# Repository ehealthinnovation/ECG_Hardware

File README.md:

ECG_Hardware
============

We are building ECG hardware with BTLE

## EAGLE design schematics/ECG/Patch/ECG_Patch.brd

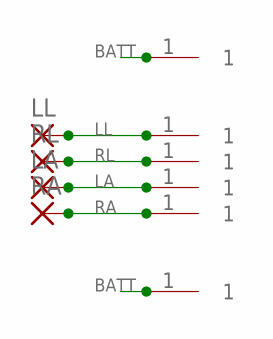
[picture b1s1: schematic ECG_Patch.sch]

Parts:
LA: 1,6/0,8
LL: 1,6/0,8
P1, P2, P3, P4, P5, P6: PISTON_RA_TH
RA: 1,6/0,8
RL: 1,6/0,8

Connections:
BATT: P1.1, P6.1
LA: LA.1, P4.1
LL: LL.1, P3.1
RA: P5.1, RA.1
RL: P2.1, RL.1

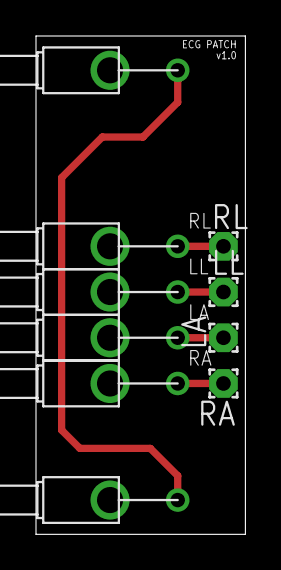
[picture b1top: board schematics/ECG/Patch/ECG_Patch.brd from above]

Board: 2 copper layers, 11.6 x 27.7 mm, 10 parts (0 on the bottom side), 5 nets.

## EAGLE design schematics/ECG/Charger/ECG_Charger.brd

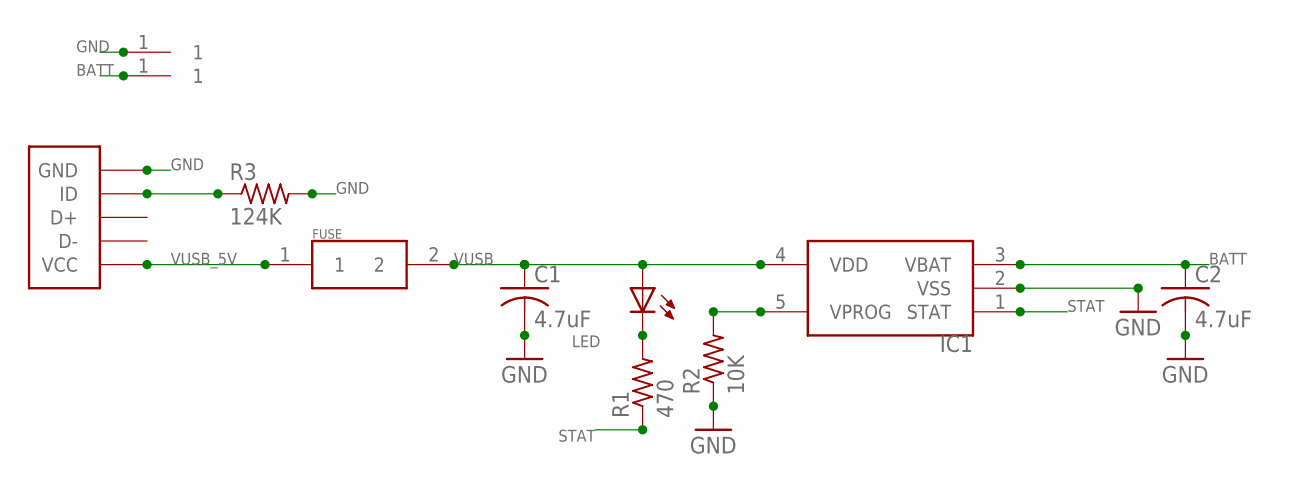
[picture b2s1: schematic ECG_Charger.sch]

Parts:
C1, C2: 4.7uF; C0402
CONN1, CONN2: PISTON_RA_TH
CONN3: USB_MICROC; USB_MICROB_FEMALE_RA_SMT
FUSE: FUSE-MF_SERIES; 1206
IC1: MCP73832_SOT23-5; SOT23-5
LED: LED_SMT_0805; SMT_LED_0805
R1: 470; R0402
R2: 10K; R0402
R3: 124K; R0402

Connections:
BATT: C2.1, CONN2.1, IC1.3 (VBAT)
GND: C1.2, C2.2, CONN1.1, CONN3.P$5 (GND), IC1.2 (VSS), R2.1, R3.2
unnamed: CONN3.P$4 (ID), R3.1
unnamed: LED.C, R1.2
STAT: IC1.1 (STAT), R1.1
VPROG: IC1.5 (VPROG), R2.2
VUSB: C1.1, FUSE.2, IC1.4 (VDD), LED.A
VUSB_5V: CONN3.P$1 (VCC), FUSE.1

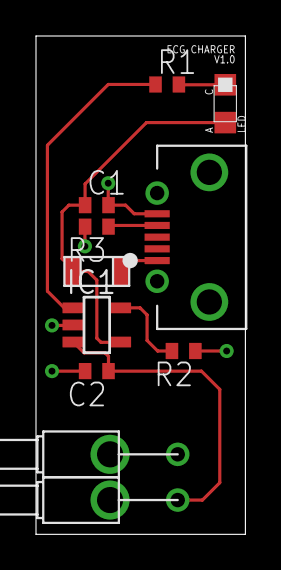
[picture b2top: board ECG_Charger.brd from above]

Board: 2 copper layers, 11.6 x 27.7 mm, 11 parts (0 on the bottom side), 8 nets.

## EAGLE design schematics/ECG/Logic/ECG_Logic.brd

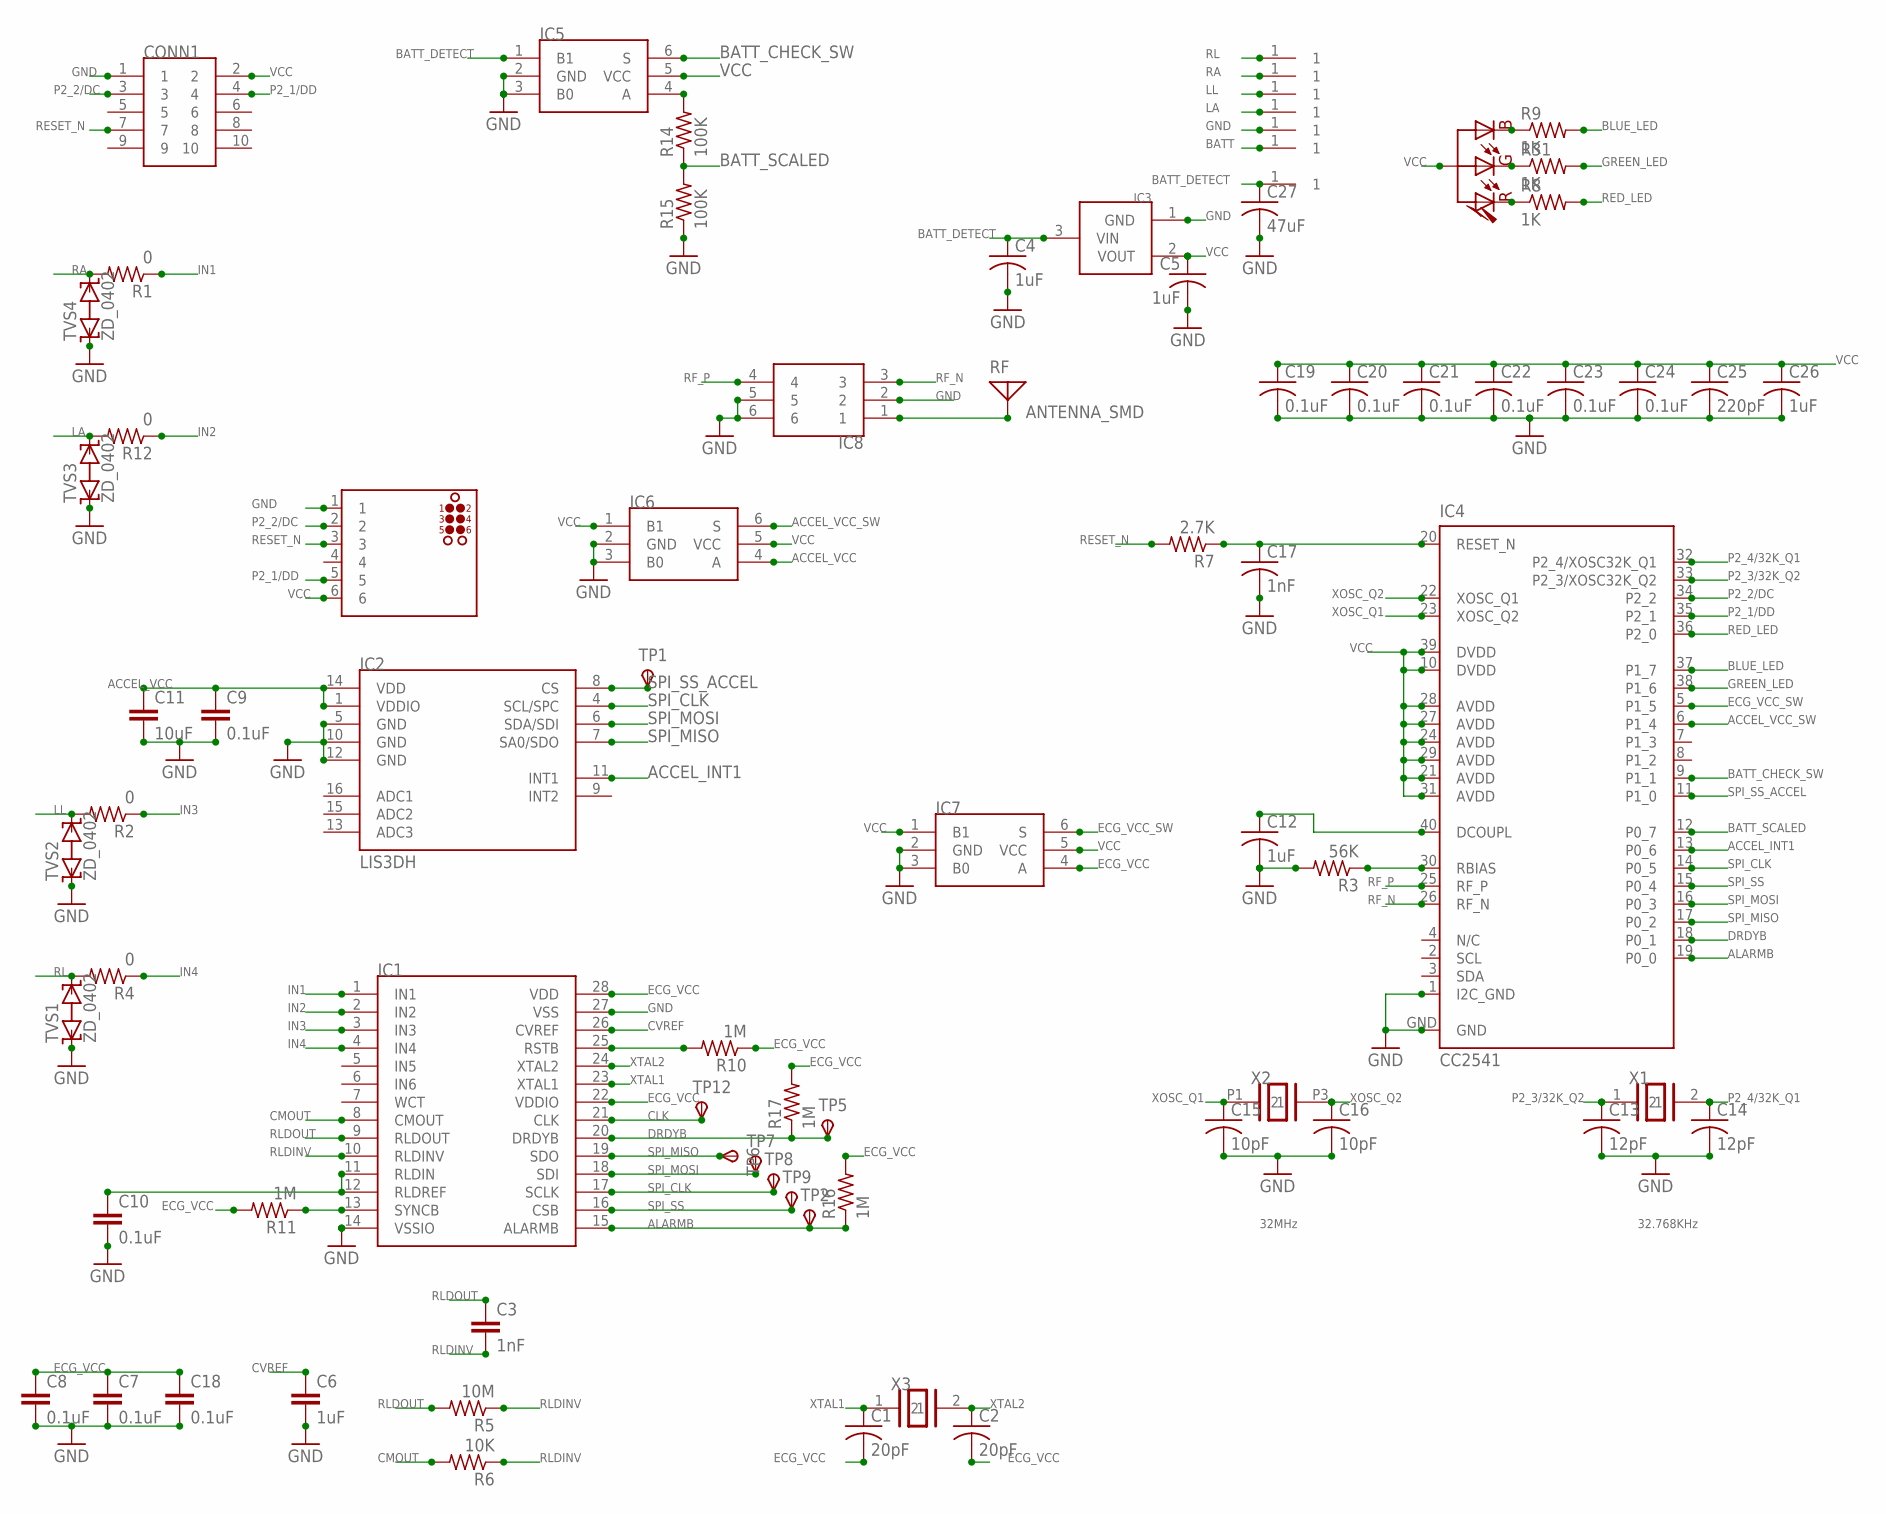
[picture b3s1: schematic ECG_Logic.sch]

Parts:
C1, C2: 20pF; C0201
C3, C17: 1nF; C0201
C4, C5, C6, C12, C26: 1uF; C0201
C7, C8, C9, C10, C18, C19, C20, C21, C22, C23, C24: 0.1uF; C0201
C11: 10uF; C0402
C13, C14: 12pF; C0201
C15, C16: 10pF; C0201
C25: 220pF; C0201
C27: 47uF; C0805
CONN1: 10POS_1.27MM_SMD; 1.27MM_SMD
IC1: ADS1293; WQFN28
IC2: LIS3DH; LGA16-3MM
IC3: MCP1703; SOT23
IC4: CC2541; RHA_S-PVQFN-N40
IC5, IC6, IC7: FSA4157; SC70-6
IC8: BALUN_2450BM_SERIES_SMD; BALUN_SMD_2450BM_SERIES
P1, P2, P3, P4, P5, P6, P7: TARGET_RA
PROG: TC2030-MCP-NL
R1, R2, R4, R12: 0; R0201
R3: 56K; R0201
R5: 10M; R0201
R6: 10K; R0201
R7: 2.7K; R0201
R8, R9, R31: 1K; R0201
R10, R11, R16, R17: 1M; R0201
R14, R15: 100K; R0201
RF: ANTENNA_SMD
TP1, TP5, TP6, TP7, TP8, TP9: TPSTP08SQ; TP08SQ
TP2, TP12: TPSTP06R; TP06R
TRI_LED: SML-LX0404SIUPGUSB
TVS1, TVS2, TVS3, TVS4: ZD_0402; 0402
X1: XTAL-2SMD; 2-SMD
X2: XTAL_403; 4-SMD
X3: ECS-40-20-4VX

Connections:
ACCEL_INT1: IC2.11 (INT1), IC4.13 (P0_6)
ACCEL_VCC: C9.1, C11.1, IC2.1 (VDDIO), IC2.14 (VDD), IC6.4 (A)
ACCEL_VCC_SW: IC4.6 (P1_4), IC6.6 (S)
ALARMB: IC1.15 (ALARMB), IC4.19 (P0_0), R16.1, TP2.TP
BATT: P6.1
BATT_CHECK_SW: IC4.9 (P1_1), IC5.6 (S)
BATT_DETECT: C4.1, C27.1, IC3.3 (VIN), IC5.1 (B1), P7.1
BATT_SCALED: IC4.12 (P0_7), R14.1, R15.2
BLUE_LED: IC4.37 (P1_7), R9.2
CLK: IC1.21 (CLK), TP12.TP
CMOUT: IC1.8 (CMOUT), R6.2
CVREF: C6.1, IC1.26 (CVREF)
DCOUPL: C12.1, IC4.40 (DCOUPL)
DRDYB: IC1.20 (DRDYB), IC4.18 (P0_1), R17.1, TP5.TP
ECG_VCC: C1.2, C2.2, C7.1, C8.1, C18.1, IC1.22 (VDDIO), IC1.28 (VDD), IC7.4 (A), R10.1, R11.2, R16.2, R17.2
ECG_VCC_SW: IC4.5 (P1_5), IC7.6 (S)
GND: C4.2, C5.2, C6.2, C7.2, C8.2, C9.2, C10.2, C11.2, C12.2, C13.2, C14.2, C15.2, C16.2, C17.2, C18.2, C19.2, C20.2, C21.2, C22.2, C23.2, C24.2, C25.2, C26.2, C27.2, CONN1.1, IC1.14 (VSSIO), IC1.27 (VSS), IC2.5 (GND), IC2.10 (GND), IC2.12 (GND), IC3.1 (GND), IC4.1 (I2C_GND), IC4.GND, IC5.2 (GND), IC5.3 (B0), IC6.2 (GND), IC6.3 (B0), IC7.2 (GND), IC7.3 (B0), IC8.2, IC8.5, IC8.6, P5.1, PROG.1, R3.2, R15.1, TVS1.1 (A), TVS2.1 (A), TVS3.1 (A), TVS4.1 (A)
GREEN_LED: IC4.38 (P1_6), R31.2
IN1: IC1.1 (IN1), R1.1
IN2: IC1.2 (IN2), R12.1
IN3: IC1.3 (IN3), R2.1
IN4: IC1.4 (IN4), R4.1
LA: P2.1, R12.2, TVS3.2 (C)
LL: P1.1, R2.2, TVS2.2 (C)
unnamed: R9.1, TRI_LED.3 (B)
unnamed: IC5.4 (A), R14.2
unnamed: IC1.25 (RSTB), R10.2
unnamed: IC8.1, RF.1
unnamed: C17.1, IC4.20 (RESET_N), R7.1
unnamed: R31.1, TRI_LED.4 (G)
unnamed: C10.1, IC1.11 (RLDIN), IC1.12 (RLDREF)
unnamed: IC1.13 (SYNCB), R11.1
unnamed: R8.1, TRI_LED.2 (R)
N/C: IC4.4 (N/C)
P2_1/DD: CONN1.4, IC4.35 (P2_1), PROG.5
P2_2/DC: CONN1.3, IC4.34 (P2_2), PROG.2
P2_3/32K_Q2: C13.1, IC4.33 (P2_3/XOSC32K_Q2), X1.1
P2_4/32K_Q1: C14.1, IC4.32 (P2_4/XOSC32K_Q1), X1.2
RA: P3.1, R1.2, TVS4.2 (C)
RED_LED: IC4.36 (P2_0), R8.2
RESET_N: CONN1.7, PROG.3, R7.2
RF_N: IC4.26 (RF_N), IC8.3
RF_P: IC4.25 (RF_P), IC8.4
RL: P4.1, R4.2, TVS1.2 (C)
RLDINV: C3.2, IC1.10 (RLDINV), R5.1, R6.1
RLDOUT: C3.1, IC1.9 (RLDOUT), R5.2
R_BIAS: IC4.30 (RBIAS), R3.1
SPI_CLK: IC1.17 (SCLK), IC2.4 (SCL/SPC), IC4.14 (P0_5), TP8.TP
SPI_MISO: IC1.19 (SDO), IC2.7 (SA0/SDO), IC4.17 (P0_2), TP6.TP
SPI_MOSI: IC1.18 (SDI), IC2.6 (SDA/SDI), IC4.16 (P0_3), TP7.TP
SPI_SS: IC1.16 (CSB), IC4.15 (P0_4), TP9.TP
SPI_SS_ACCEL: IC2.8 (CS), IC4.11 (P1_0), TP1.TP
VCC: C5.1, C19.1, C20.1, C21.1, C22.1, C23.1, C24.1, C25.1, C26.1, CONN1.2, IC3.2 (VOUT), IC4.10 (DVDD), IC4.21 (AVDD), IC4.24 (AVDD), IC4.27 (AVDD), IC4.28 (AVDD), IC4.29 (AVDD), IC4.31 (AVDD), IC4.39 (DVDD), IC5.5 (VCC), IC6.1 (B1), IC6.5 (VCC), IC7.1 (B1), IC7.5 (VCC), PROG.6, TRI_LED.1 (A)
XOSC_Q1: C15.1, IC4.23 (XOSC_Q2), X2.P1 (1)
XOSC_Q2: C16.1, IC4.22 (XOSC_Q1), X2.P3 (2)
XTAL1: C1.1, IC1.23 (XTAL1), X3.1
XTAL2: C2.1, IC1.24 (XTAL2), X3.2

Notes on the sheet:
32MHz
32.768KHz

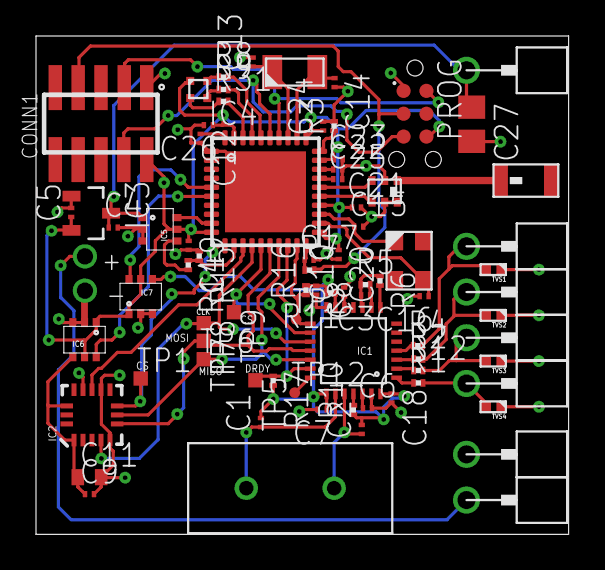
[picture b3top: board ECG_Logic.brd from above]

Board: 2 copper layers, 29.6 x 27.7 mm, 78 parts (0 on the bottom side), 55 nets.

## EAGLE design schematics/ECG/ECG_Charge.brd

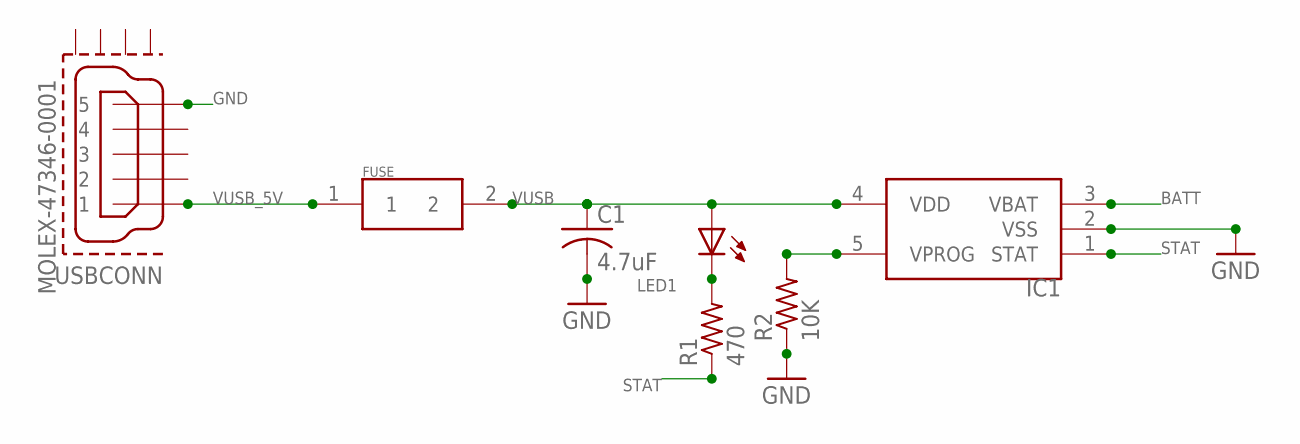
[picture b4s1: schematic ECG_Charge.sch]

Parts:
C1: 4.7uF; C0402
FUSE: FUSE-MF_SERIES; 1206
IC1: MCP73832_SOT23-5; SOT23-5
LED1: LED_SMT_0805; SMT_LED_0805
R1: 470; R0201
R2: 10K; R0201
USBCONN: MOLEX-47346-0001; MOLEX-47364-0001

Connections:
BATT: IC1.3 (VBAT)
GND: C1.2, IC1.2 (VSS), USBCONN.5
unnamed: LED1.C, R1.2
STAT: IC1.1 (STAT), R1.1
VPROG: IC1.5 (VPROG), R2.2
VSS: R2.1
VUSB: C1.1, FUSE.2, IC1.4 (VDD), LED1.A
VUSB_5V: FUSE.1, USBCONN.1

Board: 2 copper layers, 7 parts (7 on the bottom side), 6 nets, no tracks yet.

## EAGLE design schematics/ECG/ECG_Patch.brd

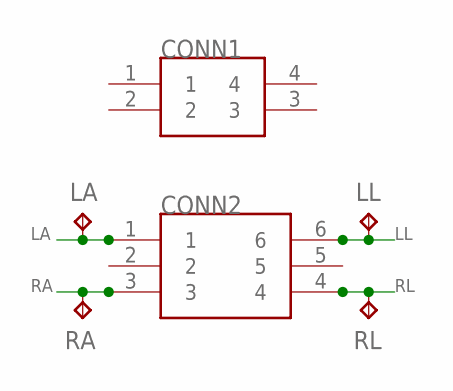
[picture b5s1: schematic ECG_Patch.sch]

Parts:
CONN1: M80-4V; M80-4-V
CONN2: M80-6V; M80-6-V
LA: TPTP20R; TP20R
LL: TPTP20R; TP20R
RA: TPTP20R; TP20R
RL: TPTP20R; TP20R

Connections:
LA: CONN2.1, LA.TP
LL: CONN2.6, LL.TP
RA: CONN2.3, RA.TP
RL: CONN2.4, RL.TP

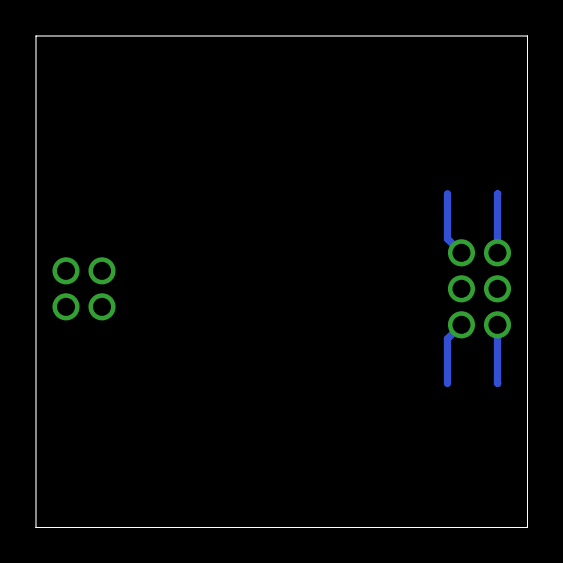
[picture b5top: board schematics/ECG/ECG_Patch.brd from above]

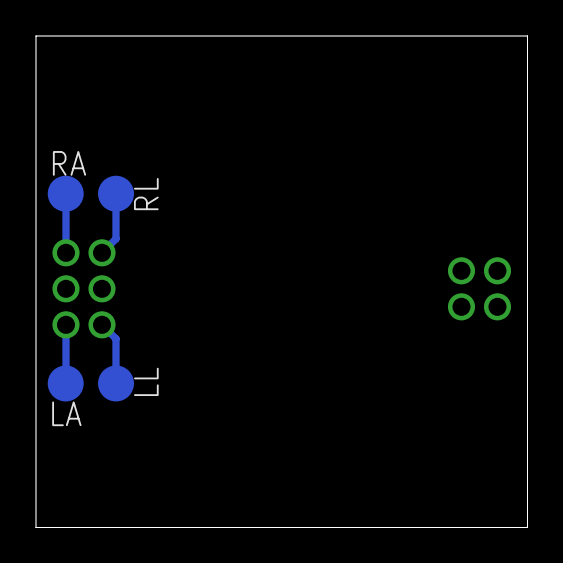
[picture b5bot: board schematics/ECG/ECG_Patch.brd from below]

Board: 4 copper layers, 27.3 x 27.3 mm, 6 parts (4 on the bottom side), 4 nets.

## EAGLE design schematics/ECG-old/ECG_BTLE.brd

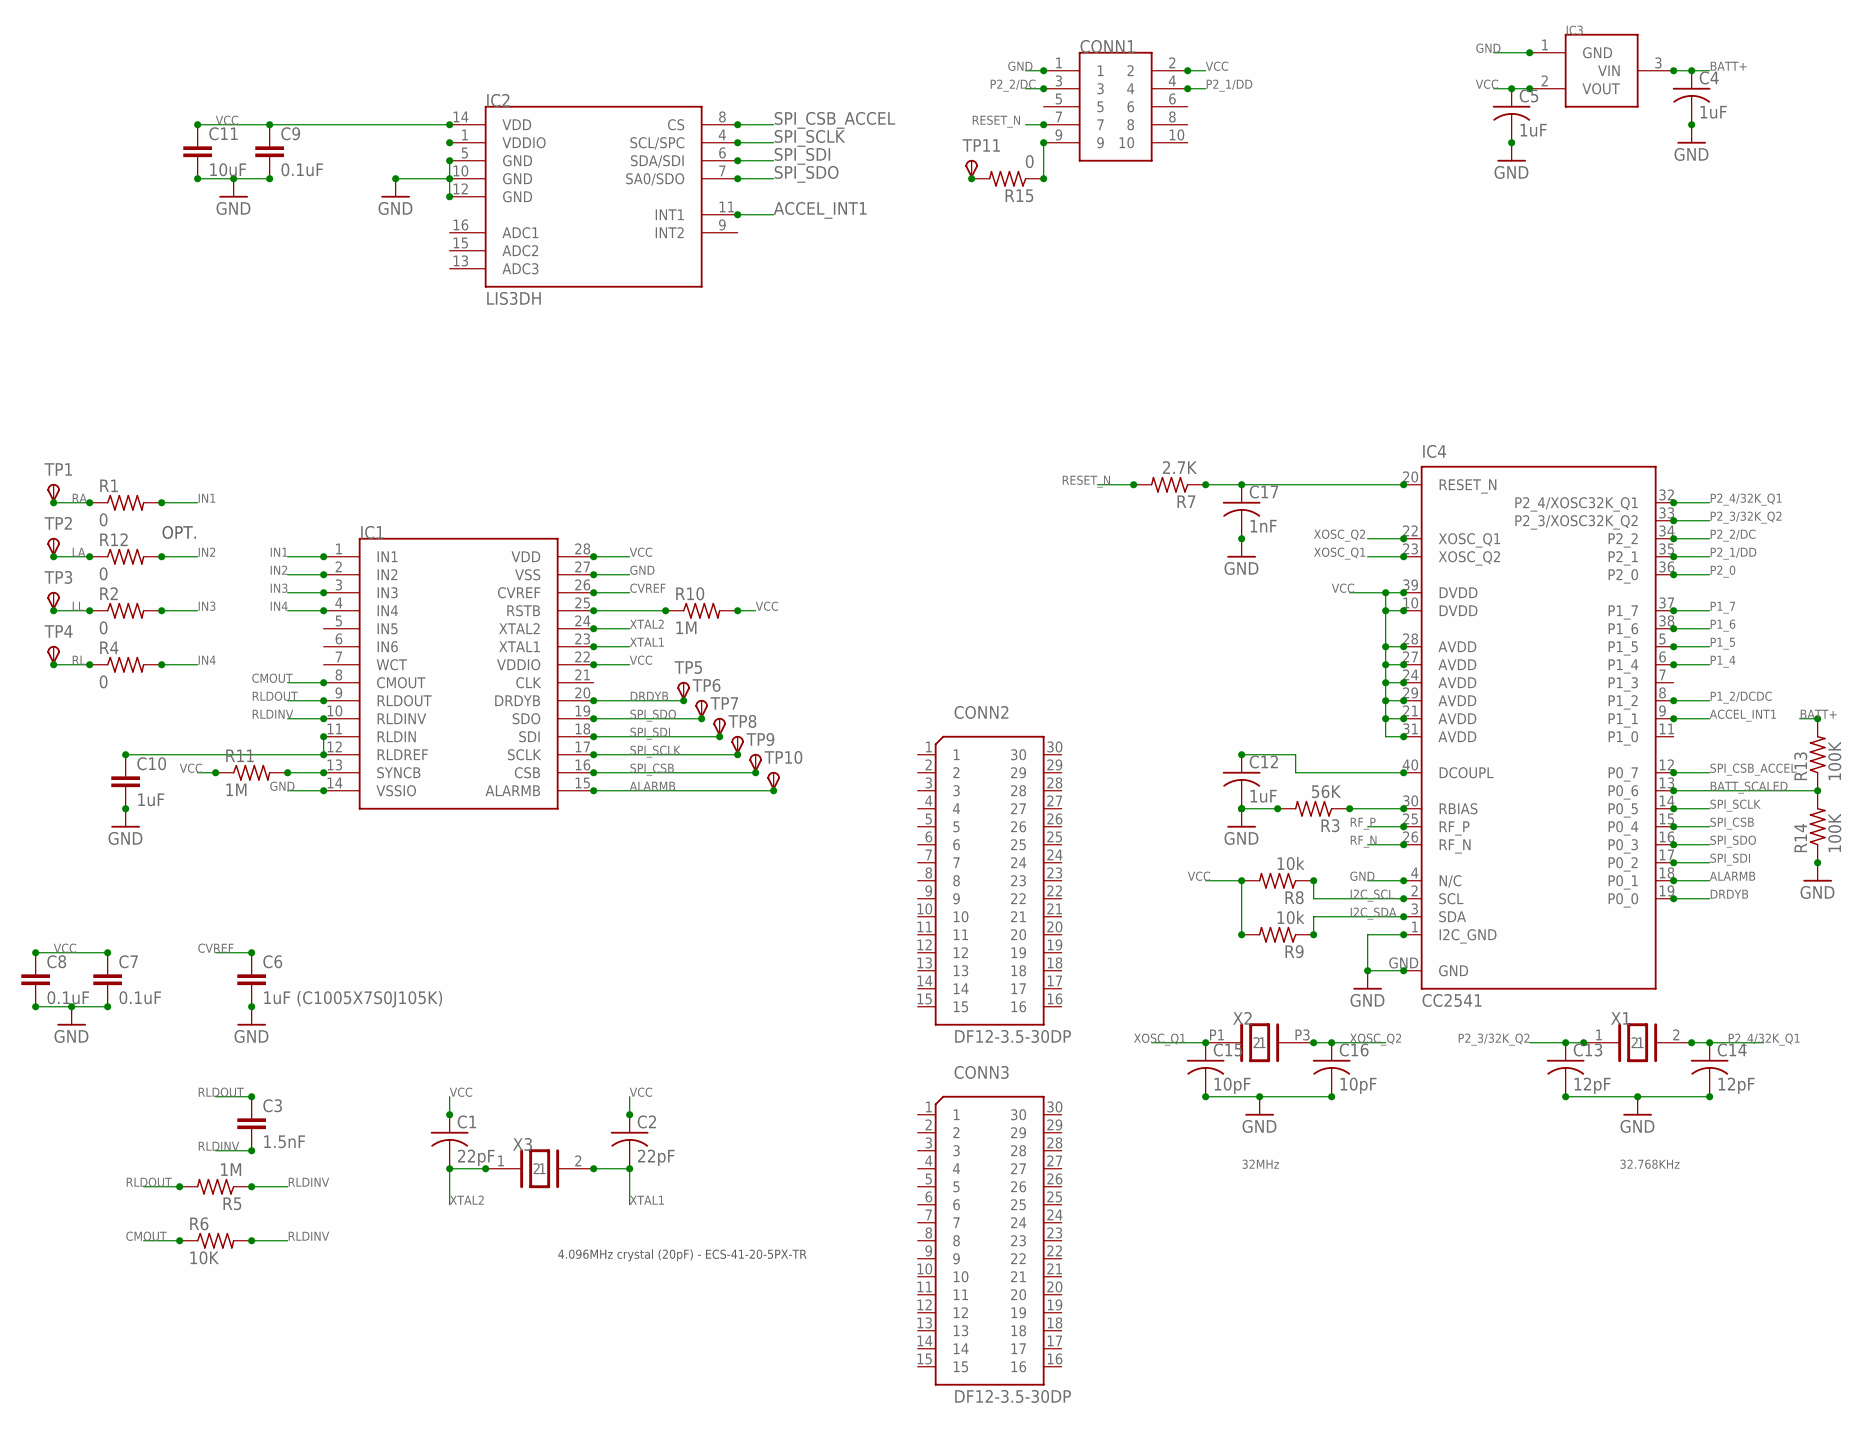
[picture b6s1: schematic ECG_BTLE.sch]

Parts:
C1, C2: 22pF; C0201
C3: 1.5nF; C0402
C4, C5: 1uF; C0201
C6: 1uF (C1005X7S0J105K); C0402
C7, C8, C9: 0.1uF; C0402
C10, C12: 1uF; C0402
C11: 10uF; C0402
C13, C14: 12pF; C0201
C15, C16: 10pF; C0201
C17: 1nF; C0402
CONN1: 10POS_1.27MM_SMD; 1.27MM_SMD
CONN2, CONN3: DF12-3.5-30DP
IC1: ADS1293; WQFN28
IC2: LIS3DH; LGA16-3MM
IC3: MCP1703; SOT23
IC4: CC2541; RHA_S-PVQFN-N40
R1, R2, R4, R12: 0; R0402
R3: 56K; R0201
R5: 1M; R0603
R6: 10K; R0402
R7: 2.7K; R0201
R8, R9: 10k; R0201
R10, R11: 1M; R0402
R13, R14: 100K; R0201
R15: 0; R0201
TP1, TP2, TP3, TP4, TP5, TP6, TP7, TP8, TP9, TP10, TP11: TPSTP08SQ; TP08SQ
X1: XTAL-2SMD; 2-SMD
X2: XTAL_403; 4-SMD
X3: XTAL-CSM7; CSM-7

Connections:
ACCEL_INT1: IC2.11 (INT1), IC4.9 (P1_1)
ALARMB: IC1.15 (ALARMB), IC4.18 (P0_1), TP10.TP
BATT+: C4.1, IC3.3 (VIN), R13.2
BATT_SCALED: IC4.13 (P0_6), R13.1, R14.2
CMOUT: IC1.8 (CMOUT), R6.1
CVREF: C6.1, IC1.26 (CVREF)
DCOUPL1: C12.1, IC4.40 (DCOUPL)
DRDYB: IC1.20 (DRDYB), IC4.19 (P0_0), TP5.TP
GND: C4.2, C5.2, C6.2, C7.2, C8.2, C9.2, C10.2, C11.2, C12.2, C13.2, C14.2, C15.2, C16.2, C17.2, CONN1.1, IC1.14 (VSSIO), IC1.27 (VSS), IC2.5 (GND), IC2.10 (GND), IC2.12 (GND), IC3.1 (GND), IC4.1 (I2C_GND), IC4.4 (N/C), IC4.GND, R3.2, R14.1
I2C_SCL: IC4.2 (SCL), R8.1
I2C_SDA: IC4.3 (SDA), R9.1
IN1: IC1.1 (IN1), R1.2
IN2: IC1.2 (IN2), R12.2
IN3: IC1.3 (IN3), R2.2
IN4: IC1.4 (IN4), R4.2
LA: R12.1, TP2.TP
LL: R2.1, TP3.TP
unnamed: CONN1.9, R15.1
unnamed: R15.2, TP11.TP
unnamed: IC1.25 (RSTB), R10.1
unnamed: C17.1, IC4.20 (RESET_N), R7.1
unnamed: C10.1, IC1.11 (RLDIN), IC1.12 (RLDREF)
unnamed: IC1.13 (SYNCB), R11.2
P1_2/DCDC: IC4.8 (P1_2)
P1_4: IC4.6 (P1_4)
P1_5: IC4.5 (P1_5)
P1_6: IC4.38 (P1_6)
P1_7: IC4.37 (P1_7)
P2_0: IC4.36 (P2_0)
P2_1/DD: CONN1.4, IC4.35 (P2_1)
P2_2/DC: CONN1.3, IC4.34 (P2_2)
P2_3/32K_Q2: C13.1, IC4.33 (P2_3/XOSC32K_Q2), X1.1
P2_4/32K_Q1: C14.1, IC4.32 (P2_4/XOSC32K_Q1), X1.2
RA: R1.1, TP1.TP
RESET_N: CONN1.7, R7.2
RF_N: IC4.26 (RF_N)
RF_P: IC4.25 (RF_P)
RL: R4.1, TP4.TP
RLDINV: C3.2, IC1.10 (RLDINV), R5.1, R6.2
RLDOUT: C3.1, IC1.9 (RLDOUT), R5.2
R_BIAS: IC4.30 (RBIAS), R3.1
SPI_CSB: IC1.16 (CSB), IC4.15 (P0_4), TP9.TP
SPI_CSB_ACCEL: IC2.8 (CS), IC4.12 (P0_7)
SPI_SCLK: IC1.17 (SCLK), IC2.4 (SCL/SPC), IC4.14 (P0_5), TP8.TP
SPI_SDI: IC1.18 (SDI), IC2.6 (SDA/SDI), IC4.17 (P0_2), TP7.TP
SPI_SDO: IC1.19 (SDO), IC2.7 (SA0/SDO), IC4.16 (P0_3), TP6.TP
VCC: C1.1, C2.1, C5.1, C7.1, C8.1, C9.1, C11.1, CONN1.2, IC1.22 (VDDIO), IC1.28 (VDD), IC2.14 (VDD), IC3.2 (VOUT), IC4.10 (DVDD), IC4.21 (AVDD), IC4.24 (AVDD), IC4.27 (AVDD), IC4.28 (AVDD), IC4.29 (AVDD), IC4.31 (AVDD), IC4.39 (DVDD), R8.2, R9.2, R10.2, R11.1
XOSC_Q1: C15.1, IC4.23 (XOSC_Q2), X2.P1 (1)
XOSC_Q2: C16.1, IC4.22 (XOSC_Q1), X2.P3 (2)
XTAL1: C2.2, IC1.23 (XTAL1), X3.2
XTAL2: C1.2, IC1.24 (XTAL2), X3.1

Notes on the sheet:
4.096MHz crystal (20pF) - ECS-41-20-5PX-TR
32MHz
32.768KHz
OPT.

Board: 2 copper layers, 53 parts (0 on the bottom side), 43 nets, no tracks yet.

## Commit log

2012-12-05 Working firmware code for ADS1292 eval board.
2012-12-07 updated directory structure for project
2012-12-07 updated deleted files in repo
2012-12-07 started schematic drawings
2012-12-07 added gitignore file
2013-01-29 schematic update
2013-01-30 adding individual BLE components instead of module for space saving purposes
2013-02-06 Adding QRS Detection Code
    Visual Studio 2012 Win32 Console application (C++)
2013-02-06 Revert "Adding QRS Detection Code"
    This reverts commit 5f6a4fcdb8681540cfaf8a76ea1cbae2c1b797e7.
2013-02-06 Adding QRS Detection Application
    Visual Studio 2012 Project
2013-02-09 Updated qrsDetect to include time domain HRV Analysis (not real-time)
2013-02-20 Added the basics of Frequency Domain HRV Analysis (untested)
    Includes interpolation, FFT and power spectrum, parts of which are based
    of Moussa's code.
2013-05-02 Modified QRSDetect to be Real Time in operation for QRS detection
    This version only does qrs detection, but it modularizes the code,
    unlike QRSDetect, which is one massive file.
2013-05-10 Removed bugs related to QRS detection
2013-05-27 added board to board connectors, removed BLE module
2013-06-14 few changes
2013-07-04 removed some unused parts
2013-07-09 updated board, added BOM template
2013-08-28 added a number of notes to the schematic and board before finishing the design
2013-09-06 added analog switch for ads1293 power. added jumper for ads1293 xtal gnd/vcc connection
2013-09-09 replaced 6 pin power header with 4 pin. added ESD protection diodes to circuit input
2013-09-10 removed cc2541 ground on pin 4. added balun and antenna
2013-09-13 components placed in ideal positions for routing
2013-09-13 moved cc2541 crystal closer to chip
2013-09-16 continued routing
2013-09-16 board routed, still requires 50ohm ble antenna trace
2013-09-17 adjusted board size. changed eeg pins
2013-09-17 created ecg patch board
2013-09-17 changed usb to micro usb, placed components in board area
2013-09-18 added TP to ALARMB pin
2013-09-18 updated bom
2013-09-18 added 4 pin smt header
2013-09-19 completed ecg logic board bom
2013-09-19 added 50ohm antenna trace. renamed TVS components
2013-09-19 reorganized schematics folders. Generated logic board v1.0 gerber zip file
2013-09-19 started assembly diagram
2013-09-20 updated assembly diagram with all components labelled
2013-09-20 removed old schematics
2013-09-23 moved batt scaled wire to ADC port 0 pin, updated routing. new gerbers generated for ordering v1.0 board
2013-09-25 updated assembly diagram, was missing a few labels
2013-10-17 Uploaded the default project
2013-10-18 Updated BLE Code wth SPI Read/Write (untested)
2013-11-04 changed 4 pin to through hole and added v1.0 marking
2013-11-14 routed charger board
2013-11-14 added comments to board
2013-11-20 replaced ADS1293 crystal with LTC6907. Fixed 6 pin programming header wiring
2013-11-22 replaced vertical headers with right angle spring loaded headers. routed osc power to pin2 of cc2541
2013-11-25 switched ECG boards to spring loaded pin headers
2013-11-25 added analog switch to OSC. OSC resistor changed to 500K ohm for 400KHz operation
2013-11-25 added board detect pin, need to find proper place to route trace
2013-11-26 routed detect pin to cc2541
2013-11-26 redesigned patch board and charging board
2013-11-29 added new low profile 4Mhz xtal
2013-11-29 expanded board size for new low profile crystal. Moved ecg input targets for shorter trace lengths to ADS1293
2013-11-29 added new 4mhz low profile crystal to bom, updated c1,c2 cap part numbers
2013-11-29 updated all boards to slightly larger dimensions and new target/piston positions
2013-11-29 added blank assembly diagram for latest logic board
2013-12-02 updated logic board assembly diagram with labels for all components
2013-12-09 board only gets power when external accessory is plugged into it
2013-12-10 added 47uF cap to battery
2013-12-10 removed board comments that are no long applicable. Added missing values to scheamtic components
2013-12-10 adjusted ground plane on charger board
2013-12-11 removed unused scheamtic trace, updated BOM
2013-12-11 updated assembly diagram with C27 capacitor
2013-12-13 added latest source code to repo
2013-12-18 scaled down patch pcb. Same dimensions as charger board
2013-12-18 fixed build warning
2013-12-31 changed micro USB port
2014-01-06 tweaked traces
2014-01-06 shrunk caps and resistors to 0402 package sizes. Added 124k resistor on ID pin of USB
2014-01-06 updated device info service to better describe the ecg device
2014-01-07 added BOM for ecg charger board
2014-01-07 fixed micro usb name
2014-01-07 cleaned up the arrangement of the components on the board
2014-01-07 fixed incorrect micro usb part number. Added hyperlinks to bom
2014-01-08 RGB LED wiring was incorrect due to error in package. Using updated RGB LED package with correct wiring
2014-01-08 code clean up. Added LED logic for blue LED to indicate device advertising
2014-01-09 toggling ads1293 power correctly
2014-01-10 using updated millmax target package with correctly centered origin
2014-01-10 fixed trace angles that were effected by using modified millmax target package
2014-01-10 using updated millmax piston package with proper center origin
2014-01-10 using modified piston package with corrected origin
2014-01-10 added sketchup models of all ECG related PCBs
2014-01-13 rolled back some of the code clean up due to issue with ECG signal. ECG signal and LED advertising status working
2014-01-13 using corrected piston model
2014-01-13 using corrected target model
2014-01-13 added logic board model without 10pos programming header
2014-01-13 green LED turns on momentarily on power on. Advertising is enabled after power on LED turns off
2014-01-22 added code to initialize the LIS3DH onboard accelerometer
2014-01-28 using MS bit to read multiple axis of data from LIS3DH
2014-01-28 created accelerometer profile, requires testing
2014-01-30 turned off blue led on connection. Updated project files for accelerometer profile
2014-01-31 shortened advertising time to 500ms to improve connection times
2014-01-31 boosted the TX power and RX gain
2014-02-01 fixed accelerometer profile. Added 20ms timer for testing
2014-02-05 changed connection intervals to extend battery life
2014-02-05 added battery service profile
2014-02-05 modifying stock battery service profile to work with ECG board
2014-02-10 reduced SPI bus speed to 2MHz
2014-02-11 lowered SPI bus speed to 500Hz
2014-02-11 first round of code and comment clean up
2014-02-11 removed hal key code
2014-02-14 fixed battery level reading
2014-02-24 added timer to periodically send the battery level to the ble host
2014-02-24 adding battery check broke ecg, fixed
2014-02-27 tweaking code for optimization
2014-04-24 added lithium battery to BOM
2014-04-30 using corrected piston package
2014-04-30 updated code
2014-04-30 fixed charger board piston naming

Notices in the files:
parts and their libraries:
tagconnect: ©2009 ROFA.cz
